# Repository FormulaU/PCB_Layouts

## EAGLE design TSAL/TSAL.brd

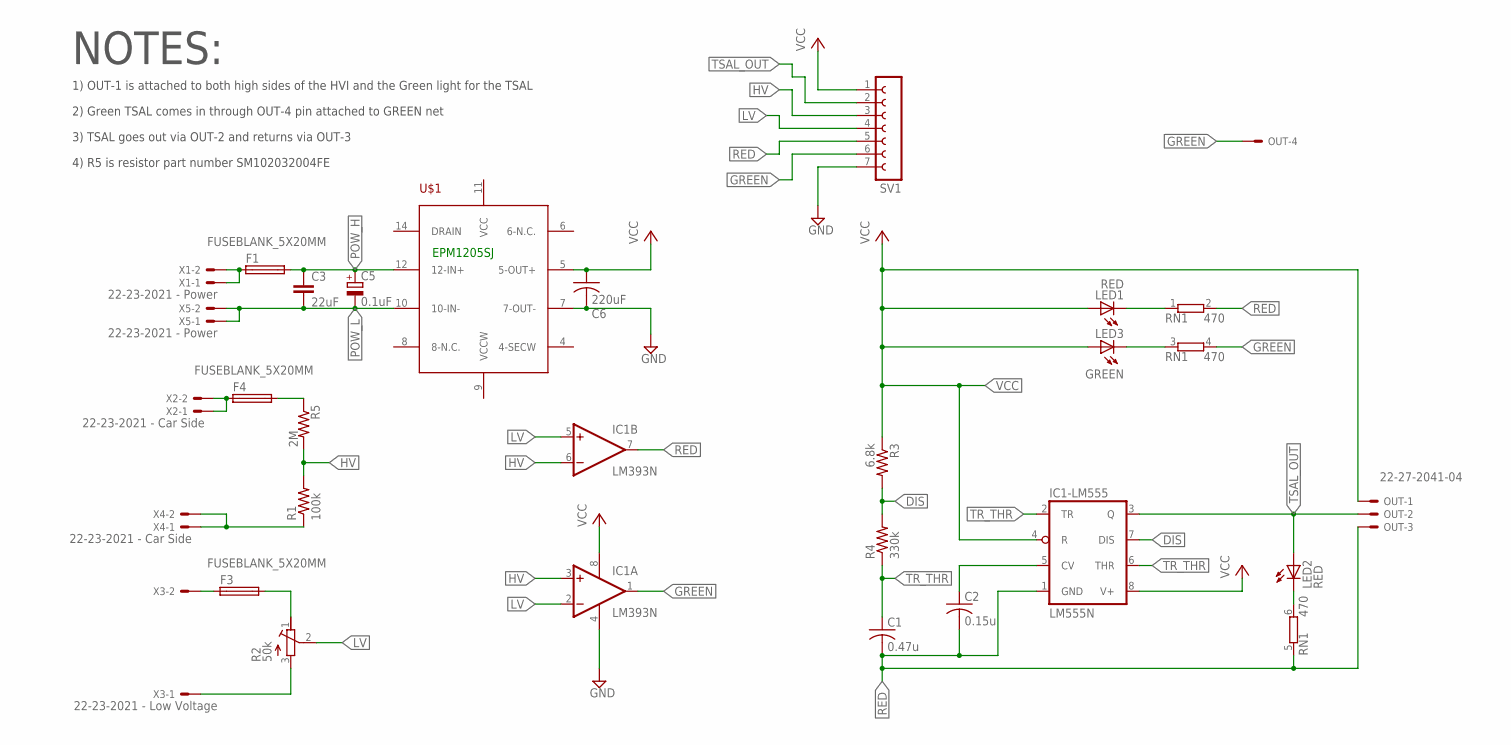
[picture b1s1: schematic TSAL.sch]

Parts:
C1: 0.47u; C050-075X075
C2: 0.15u; C050-075X075
C3: 22uF; C150-091X182
C5: 0.1uF; E7,5-16
C6: 220uF; C050-055X075
F1, F3, F4: FUSEBLANK_5X20MM; FUSE_HOLDER_5X20MM
IC1: LM393N; DIL08
IC1-LM555: LM555N; DIL08
LED1, LED2: RED; LED3MM
LED3: GREEN; LED3MM
OUT: 22-27-2041-04; 6410-04
R1: 100k; 0207/10
R2: 50k; RTRIM3006P
R3: 6.8k; 0309/12
R4: 330k; 0309/12
R5: 2M; 0207/10
RN1: 470; SIL6
SV1: FE07W
U$1: EPM1205SJ
X1, X5: 22-23-2021 - Power; 22-23-2021
X2, X4: 22-23-2021 - Car Side; 22-23-2021
X3: 22-23-2021 - Low Voltage; 22-23-2021

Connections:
DIS: IC1-LM555.7 (DIS), R3.2, R4.2
GND: C6.2, IC1.4 (V-), SV1.7, U$1.7 (7-OUT-)
GREEN: IC1.1 (OUT), OUT.4, RN1.4 (2), SV1.6
HV: IC1.3 (+IN), IC1.6 (-IN), R1.2, R5.2, SV1.3
LV: IC1.2 (-IN), IC1.5 (+IN), R2.2 (S), SV1.4
unnamed: R1.1, X4.1, X4.2
unnamed: F3.2, R2.1 (E)
unnamed: R2.3 (A), X3.1
unnamed: F4.1, X2.1, X2.2
unnamed: F3.1, X3.2
unnamed: LED3.K (C), RN1.3 (1)
unnamed: F1.1, X1.1, X1.2
unnamed: F4.2, R5.1
unnamed: C2.1, IC1-LM555.5 (CV)
unnamed: LED2.K (C), RN1.6 (2)
unnamed: LED1.K (C), RN1.1
POW_H: C3.1, C5.+, F1.2, U$1.12 (12-IN+)
POW_L: C3.2, C5.-, U$1.10 (10-IN-), X5.1, X5.2
RED: C1.2, C2.2, IC1.7 (OUT), IC1-LM555.1 (GND), OUT.3, RN1.2, RN1.5 (1), SV1.5
TR_THR: C1.1, IC1-LM555.2 (TR), IC1-LM555.6 (THR), R4.1
TSAL_OUT: IC1-LM555.3 (Q), LED2.A, OUT.2, SV1.2
VCC: C6.1, IC1.8 (V+), IC1-LM555.4 (R), IC1-LM555.8 (V+), LED1.A, LED3.A, OUT.1, R3.1, SV1.1, U$1.5 (5-OUT+)

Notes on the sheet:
EPM1205SJ
NOTES:
1) OUT-1 is attached to both high sides of the HVI and the Green light for the TSAL
2) Green TSAL comes in through OUT-4 pin attached to GREEN net
3) TSAL goes out via OUT-2 and returns via OUT-3
4) R5 is resistor part number SM102032004FE

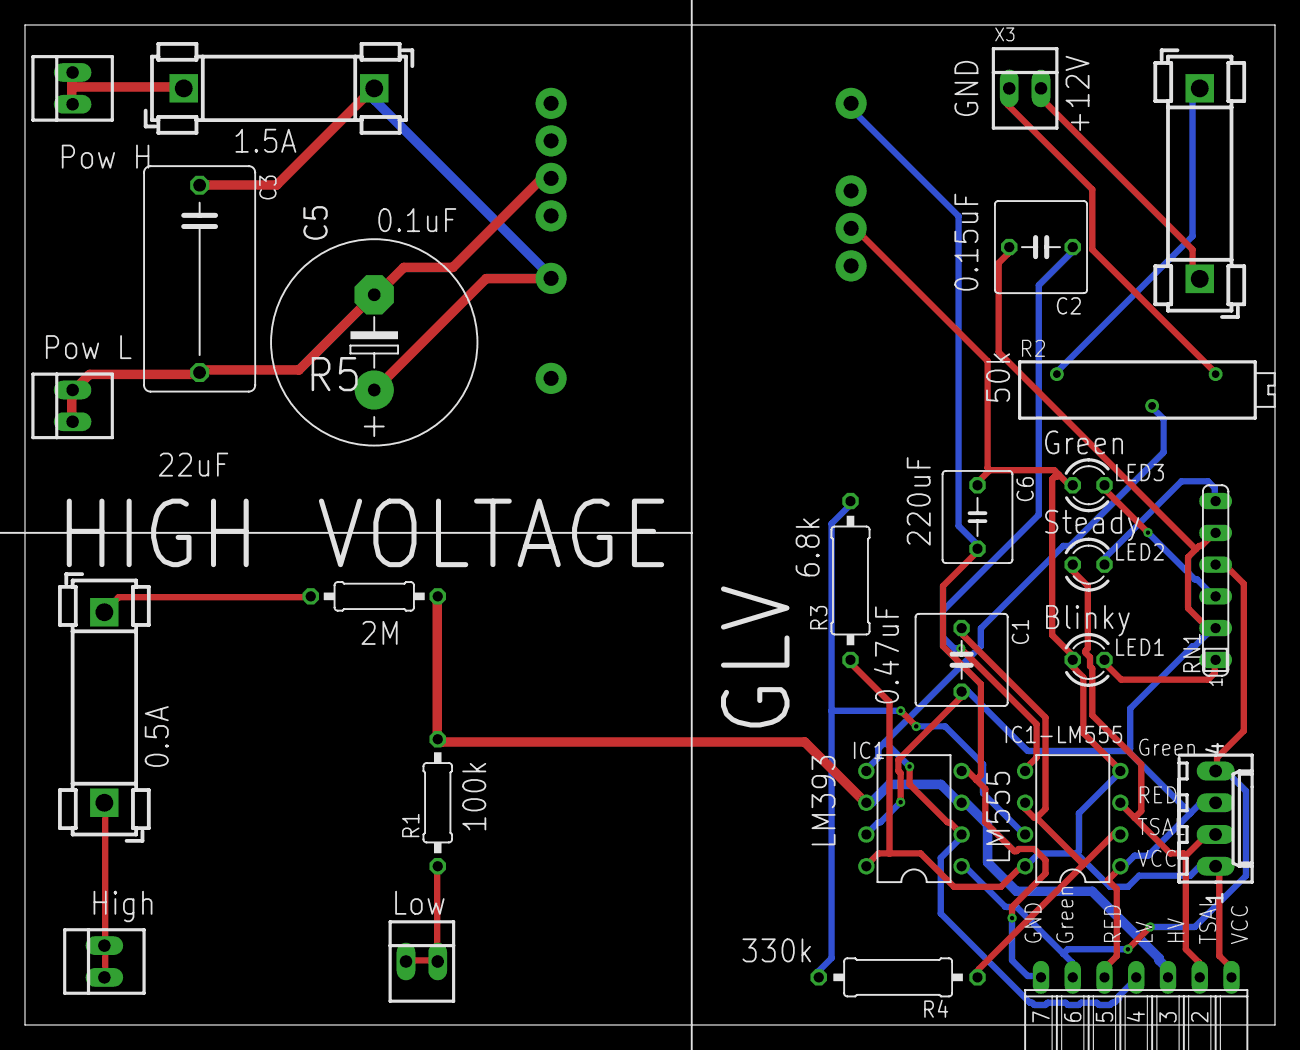
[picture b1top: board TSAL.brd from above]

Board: 2 copper layers, 100.0 x 80.0 mm, 27 parts (0 on the bottom side), 22 nets.

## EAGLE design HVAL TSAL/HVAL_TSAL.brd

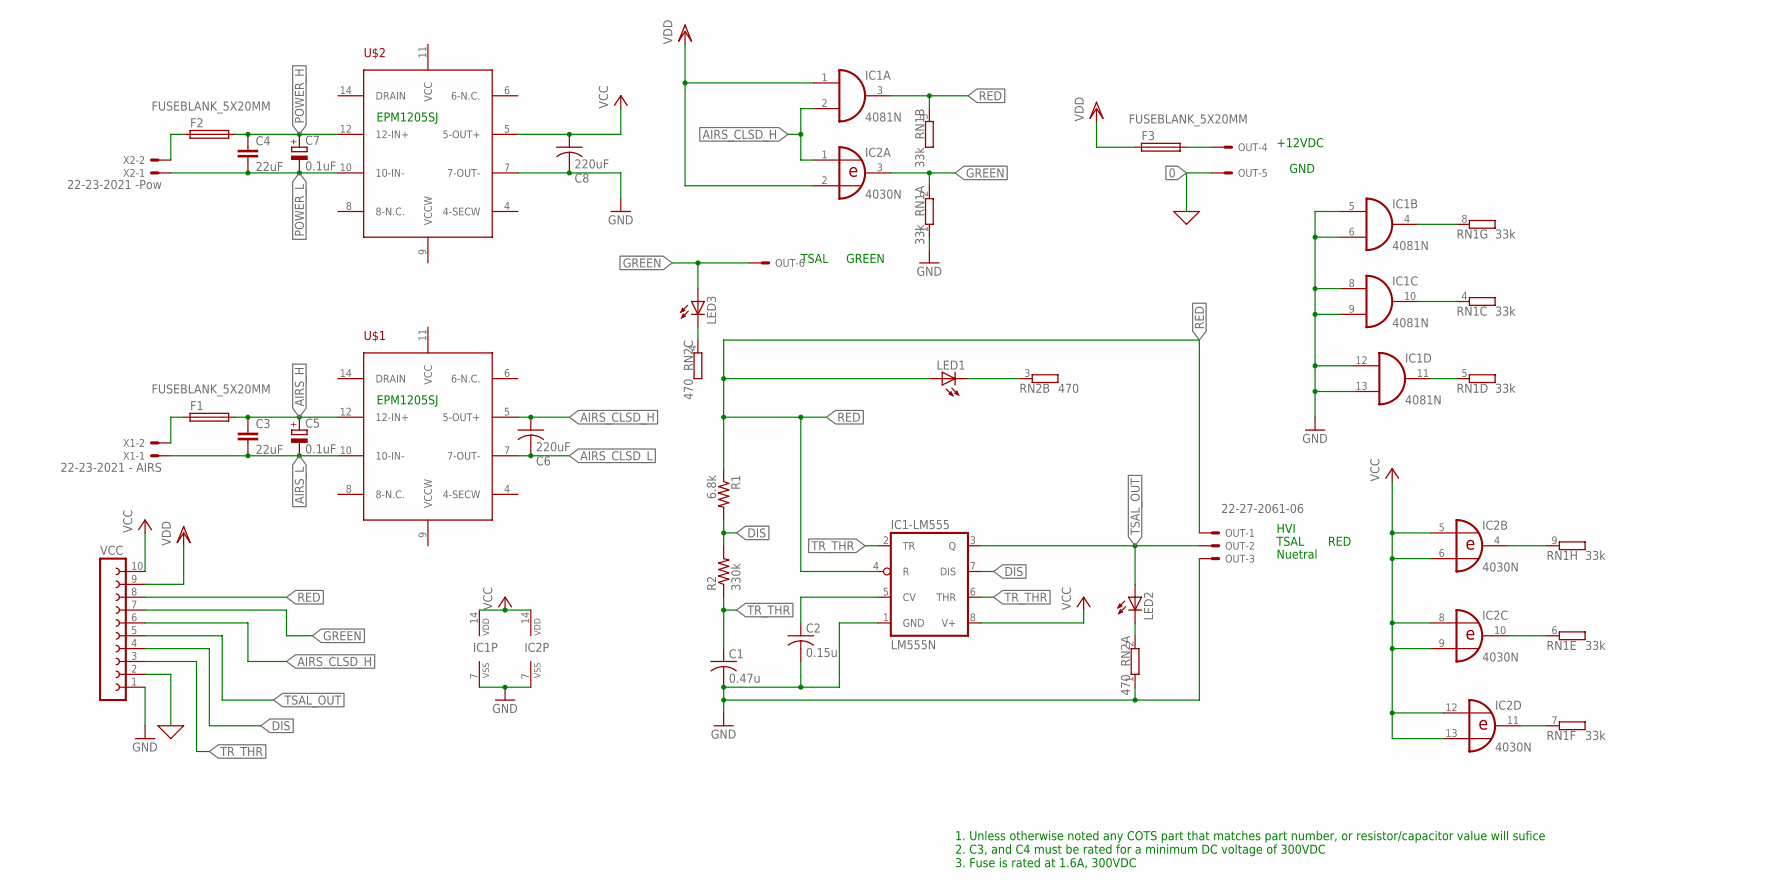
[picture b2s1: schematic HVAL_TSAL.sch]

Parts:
C1: 0.47u; C050-075X075
C2: 0.15u; C050-075X075
C3, C4: 22uF; C150-091X182
C5, C7: 0.1uF; E7,5-16
C6, C8: 220uF; C050-055X075
F1, F2, F3: FUSEBLANK_5X20MM; FUSE_HOLDER_5X20MM
IC1: 4081N; DIL14
IC1-LM555: LM555N; DIL08
IC2: 4030N; DIL14
LED1, LED2, LED3: LED3MM
OUT: 22-27-2061-06; 6410-06
R1: 6.8k; 0309/12
R2: 330k; 0309/12
RN1: 33k; SIL9
RN2: 470; SIL4
U$1, U$2: EPM1205SJ
VCC: FE10-1; FE10
X1: 22-23-2021 - AIRS; 22-23-2021
X2: 22-23-2021 -Pow; 22-23-2021

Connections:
0: OUT.5, VCC.2
AIRS_CLSD_H: C6.1, IC1.2 (I1), IC2.1 (I0), U$1.5 (5-OUT+), VCC.6
AIRS_CLSD_L: C6.2, U$1.7 (7-OUT-)
AIRS_H: C3.1, C5.+, F1.2, U$1.12 (12-IN+)
AIRS_L: C3.2, C5.-, U$1.10 (10-IN-), X1.1
DIS: IC1-LM555.7 (DIS), R1.2, R2.2, VCC.4
GND: C1.2, C2.2, C8.2, IC1.5 (I0), IC1.6 (I1), IC1.7 (VSS), IC1.8 (I0), IC1.9 (I1), IC1.12 (I0), IC1.13 (I1), IC1-LM555.1 (GND), IC2.7 (VSS), OUT.3, RN1.1, RN2.1, U$2.7 (7-OUT-), VCC.1
GREEN: IC2.3 (O), LED3.A, OUT.6, RN1.2, VCC.7
unnamed: LED2.K (C), RN2.2
unnamed: IC2.10 (O), RN1.6 (2)
unnamed: IC1.11 (O), RN1.5 (2)
unnamed: F2.1, X2.2
unnamed: F3.2, OUT.4
unnamed: IC1.10 (O), RN1.4 (2)
unnamed: C2.1, IC1-LM555.5 (CV)
unnamed: IC2.4 (O), RN1.9 (2)
unnamed: IC1.4 (O), RN1.8 (2)
unnamed: F1.1, X1.2
unnamed: IC2.11 (O), RN1.7 (2)
unnamed: LED1.K (C), RN2.3 (2)
unnamed: LED3.K (C), RN2.4 (2)
POWER_H: C4.1, C7.+, F2.2, U$2.12 (12-IN+)
POWER_L: C4.2, C7.-, U$2.10 (10-IN-), X2.1
RED: IC1.3 (O), IC1-LM555.4 (R), LED1.A, OUT.1, R1.1, RN1.3 (2), VCC.8
TR_THR: C1.1, IC1-LM555.2 (TR), IC1-LM555.6 (THR), R2.1, VCC.3
TSAL_OUT: IC1-LM555.3 (Q), LED2.A, OUT.2, VCC.5
VCC: C8.1, IC1.14 (VDD), IC1-LM555.8 (V+), IC2.5 (I0), IC2.6 (I1), IC2.8 (I0), IC2.9 (I1), IC2.12 (I0), IC2.13 (I1), IC2.14 (VDD), U$2.5 (5-OUT+), VCC.10
VDD: F3.1, IC1.1 (I0), IC2.2 (I1), VCC.9

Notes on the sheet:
EPM1205SJ
1. Unless otherwise noted any COTS part that matches part number, or resistor/capacitor value will sufice 2. C3, and C4 must be rated for a minimum DC voltage of 300VDC 3. Fuse is rated at 1.6A, 300VDC
TSAL
HVI
Nuetral
+12VDC
GND
RED
TSAL GREEN

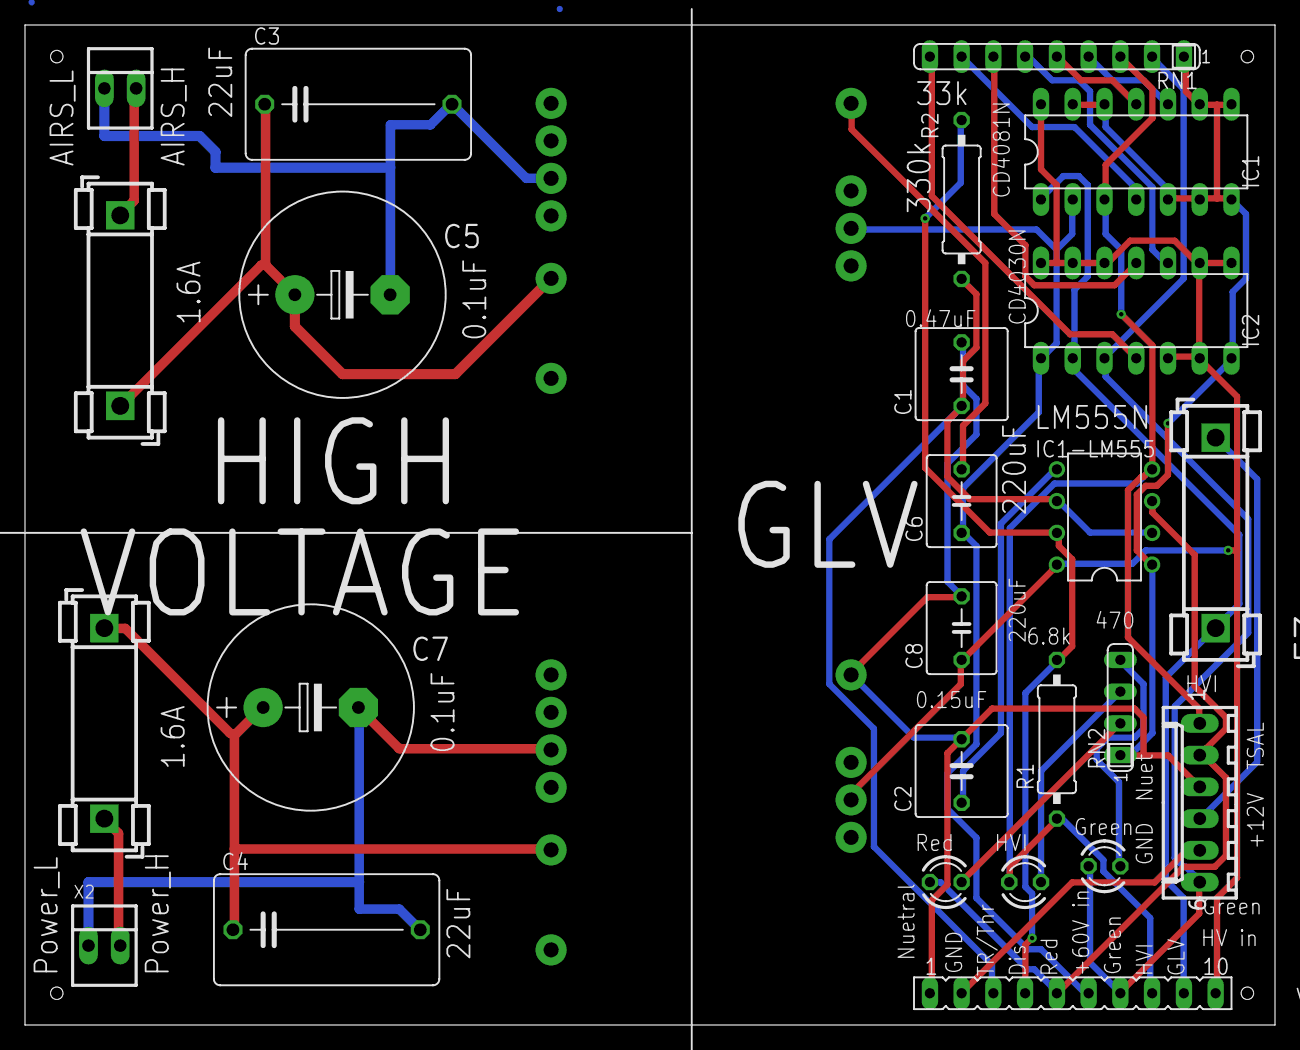
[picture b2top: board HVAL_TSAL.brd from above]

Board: 2 copper layers, 100.0 x 80.0 mm, 27 parts (0 on the bottom side), 28 nets.

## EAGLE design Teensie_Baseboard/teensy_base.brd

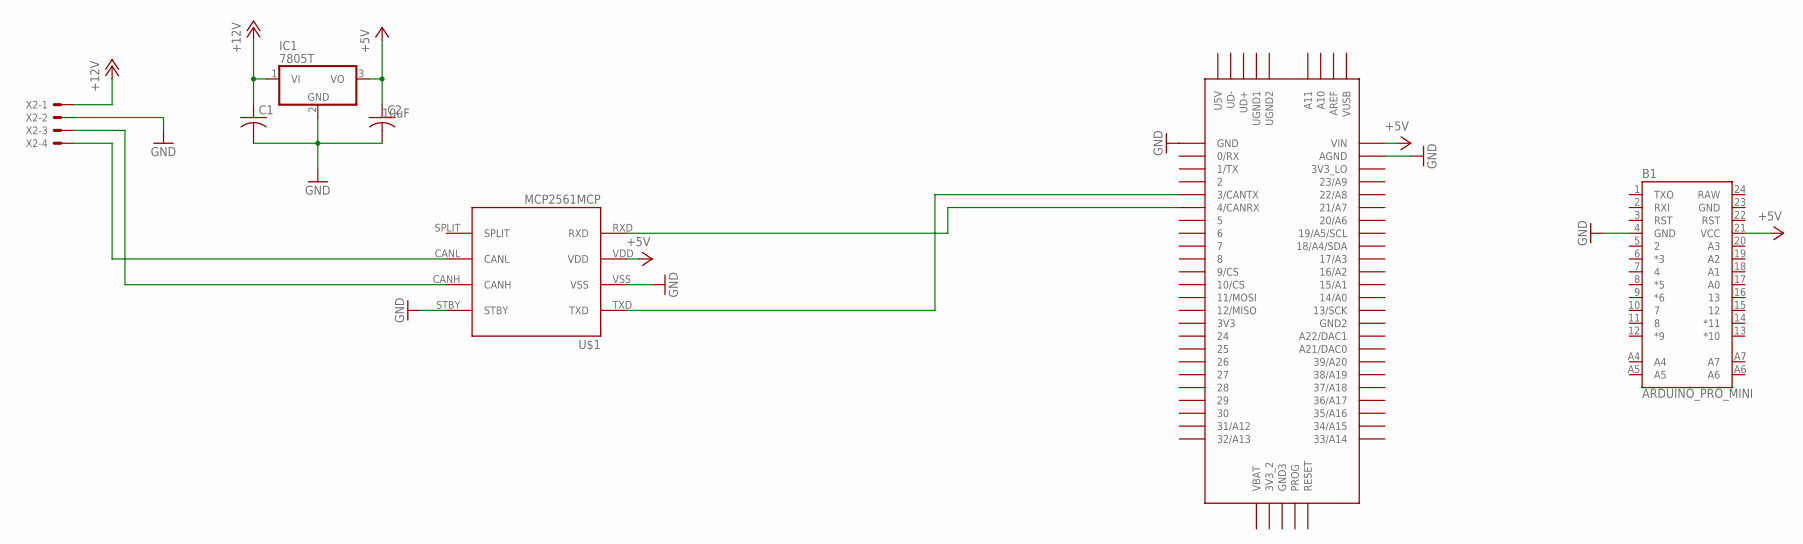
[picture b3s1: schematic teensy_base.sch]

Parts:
B1: ARDUINO_PRO_MINI
C1, C2: C-USC1206; C1206
IC1: 7805T; TO220H
U$1: MCP2561MCP; MCP2561_PDIP
U$2: TEENSY_3.5/3.6
X2: KK-156-4

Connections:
+5V: B1.21 (VCC), C2.1, IC1.3 (VO), U$1.VDD, U$2.VIN
+12V: C1.1, IC1.1 (VI), X2.1
GND: B1.4 (GND), B1.23 (GND), C1.2, C2.2, IC1.2 (GND), U$1.STBY, U$1.VSS, U$2.AGND, U$2.GND, X2.2
unnamed: U$1.RXD, U$2.4/CANRX
unnamed: U$1.TXD, U$2.3/CANTX
unnamed: U$1.CANH, X2.3
unnamed: U$1.CANL, X2.4
RAW: B1.24 (RAW)

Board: 2 copper layers, 7 parts (0 on the bottom side), 7 nets, no tracks yet.

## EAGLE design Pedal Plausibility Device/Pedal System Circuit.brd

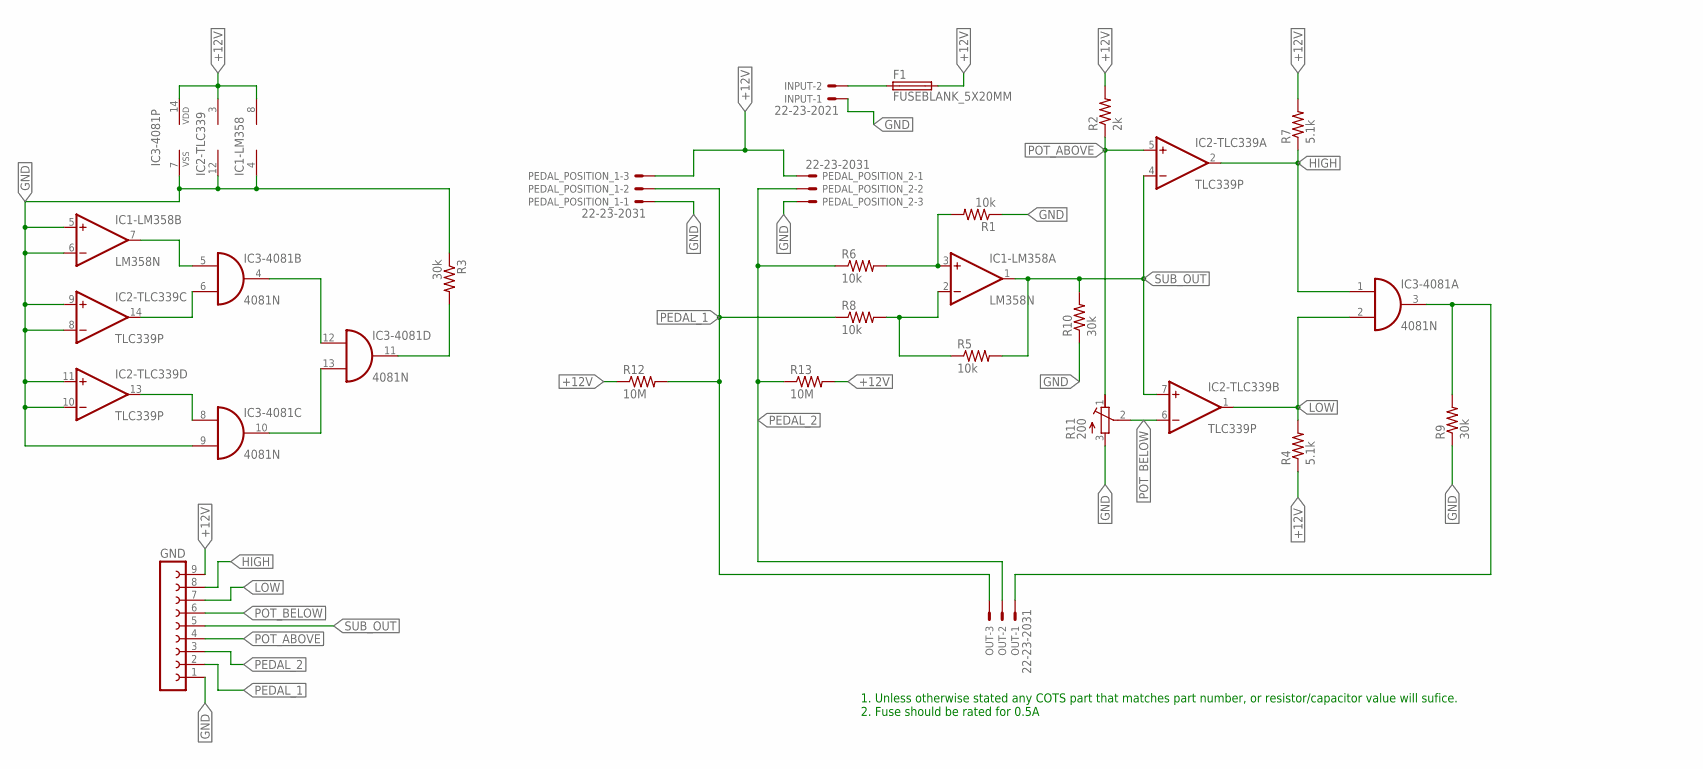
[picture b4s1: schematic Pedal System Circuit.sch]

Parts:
F1: FUSEBLANK_5X20MM; FUSE_HOLDER_5X20MM
GND: FE09W
IC1-LM358: LM358N; DIL08
IC2-TLC339: TLC339P; DIL14
IC3-4081: 4081N; DIL14
INPUT: 22-23-2021
OUT: 22-23-2031
PEDAL_POSITION_1, PEDAL_POSITION_2: 22-23-2031
R1, R5, R6, R8: 10k; 0207/12
R2: 2k; 0309/12
R3, R9, R10: 30k; 0207/12
R4, R7: 5.1k; 0207/12
R11: 200; RTRIM43P
R12, R13: 10M; 0207/12

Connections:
+12V: F1.2, GND.9, IC1-LM358.8 (V+), IC2-TLC339.3 (V+), IC3-4081.14 (VDD), PEDAL_POSITION_1.3, PEDAL_POSITION_2.1, R2.2, R4.1, R7.2, R12.1, R13.2
GND: GND.1, IC1-LM358.4 (V-), IC1-LM358.5 (+IN), IC1-LM358.6 (-IN), IC2-TLC339.8 (-IN), IC2-TLC339.9 (+IN), IC2-TLC339.10 (-IN), IC2-TLC339.11 (+IN), IC2-TLC339.12 (V-), IC3-4081.7 (VSS), IC3-4081.9 (I1), INPUT.1, PEDAL_POSITION_1.1, PEDAL_POSITION_2.3, R1.1, R3.1, R9.1, R10.1, R11.3 (A)
HIGH: GND.8, IC2-TLC339.2 (OUT), IC3-4081.1 (I0), R7.1
LOW: GND.7, IC2-TLC339.1 (OUT), IC3-4081.2 (I1), R4.2
unnamed: IC3-4081.10 (O), IC3-4081.13 (I1)
unnamed: IC3-4081.4 (O), IC3-4081.12 (I0)
unnamed: IC1-LM358.3 (+IN), R1.2, R6.2
unnamed: IC3-4081.3 (O), OUT.1, R9.2
unnamed: IC3-4081.11 (O), R3.2
unnamed: IC1-LM358.7 (OUT), IC3-4081.5 (I0)
unnamed: F1.1, INPUT.2
unnamed: IC2-TLC339.13 (OUT), IC3-4081.8 (I0)
unnamed: IC2-TLC339.14 (OUT), IC3-4081.6 (I1)
unnamed: IC1-LM358.2 (-IN), R5.1, R8.2
PEDAL_1: GND.2, OUT.3, PEDAL_POSITION_1.2, R8.1, R12.2
PEDAL_2: GND.3, OUT.2, PEDAL_POSITION_2.2, R6.1, R13.1
POT_ABOVE: GND.4, IC2-TLC339.5 (+IN), R2.1, R11.1 (E)
POT_BELOW: GND.6, IC2-TLC339.6 (-IN), R11.2 (S)
SUB_OUT: GND.5, IC1-LM358.1 (OUT), IC2-TLC339.4 (-IN), IC2-TLC339.7 (+IN), R5.2, R10.2

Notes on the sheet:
IC2-TLC339
IC1-LM358
1. Unless otherwise stated any COTS part that matches part number, or resistor/capacitor value will sufice. 2. Fuse should be rated for 0.5A

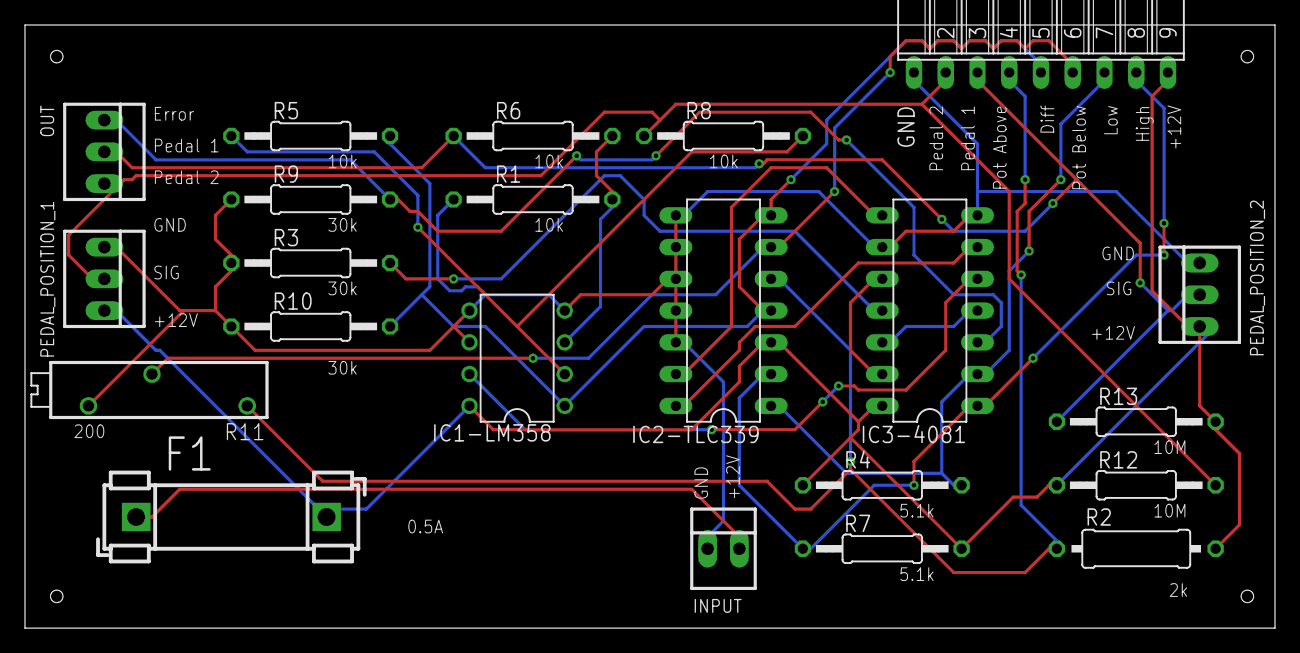
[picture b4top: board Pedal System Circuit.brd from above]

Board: 2 copper layers, 100.0 x 48.2 mm, 22 parts (0 on the bottom side), 19 nets.

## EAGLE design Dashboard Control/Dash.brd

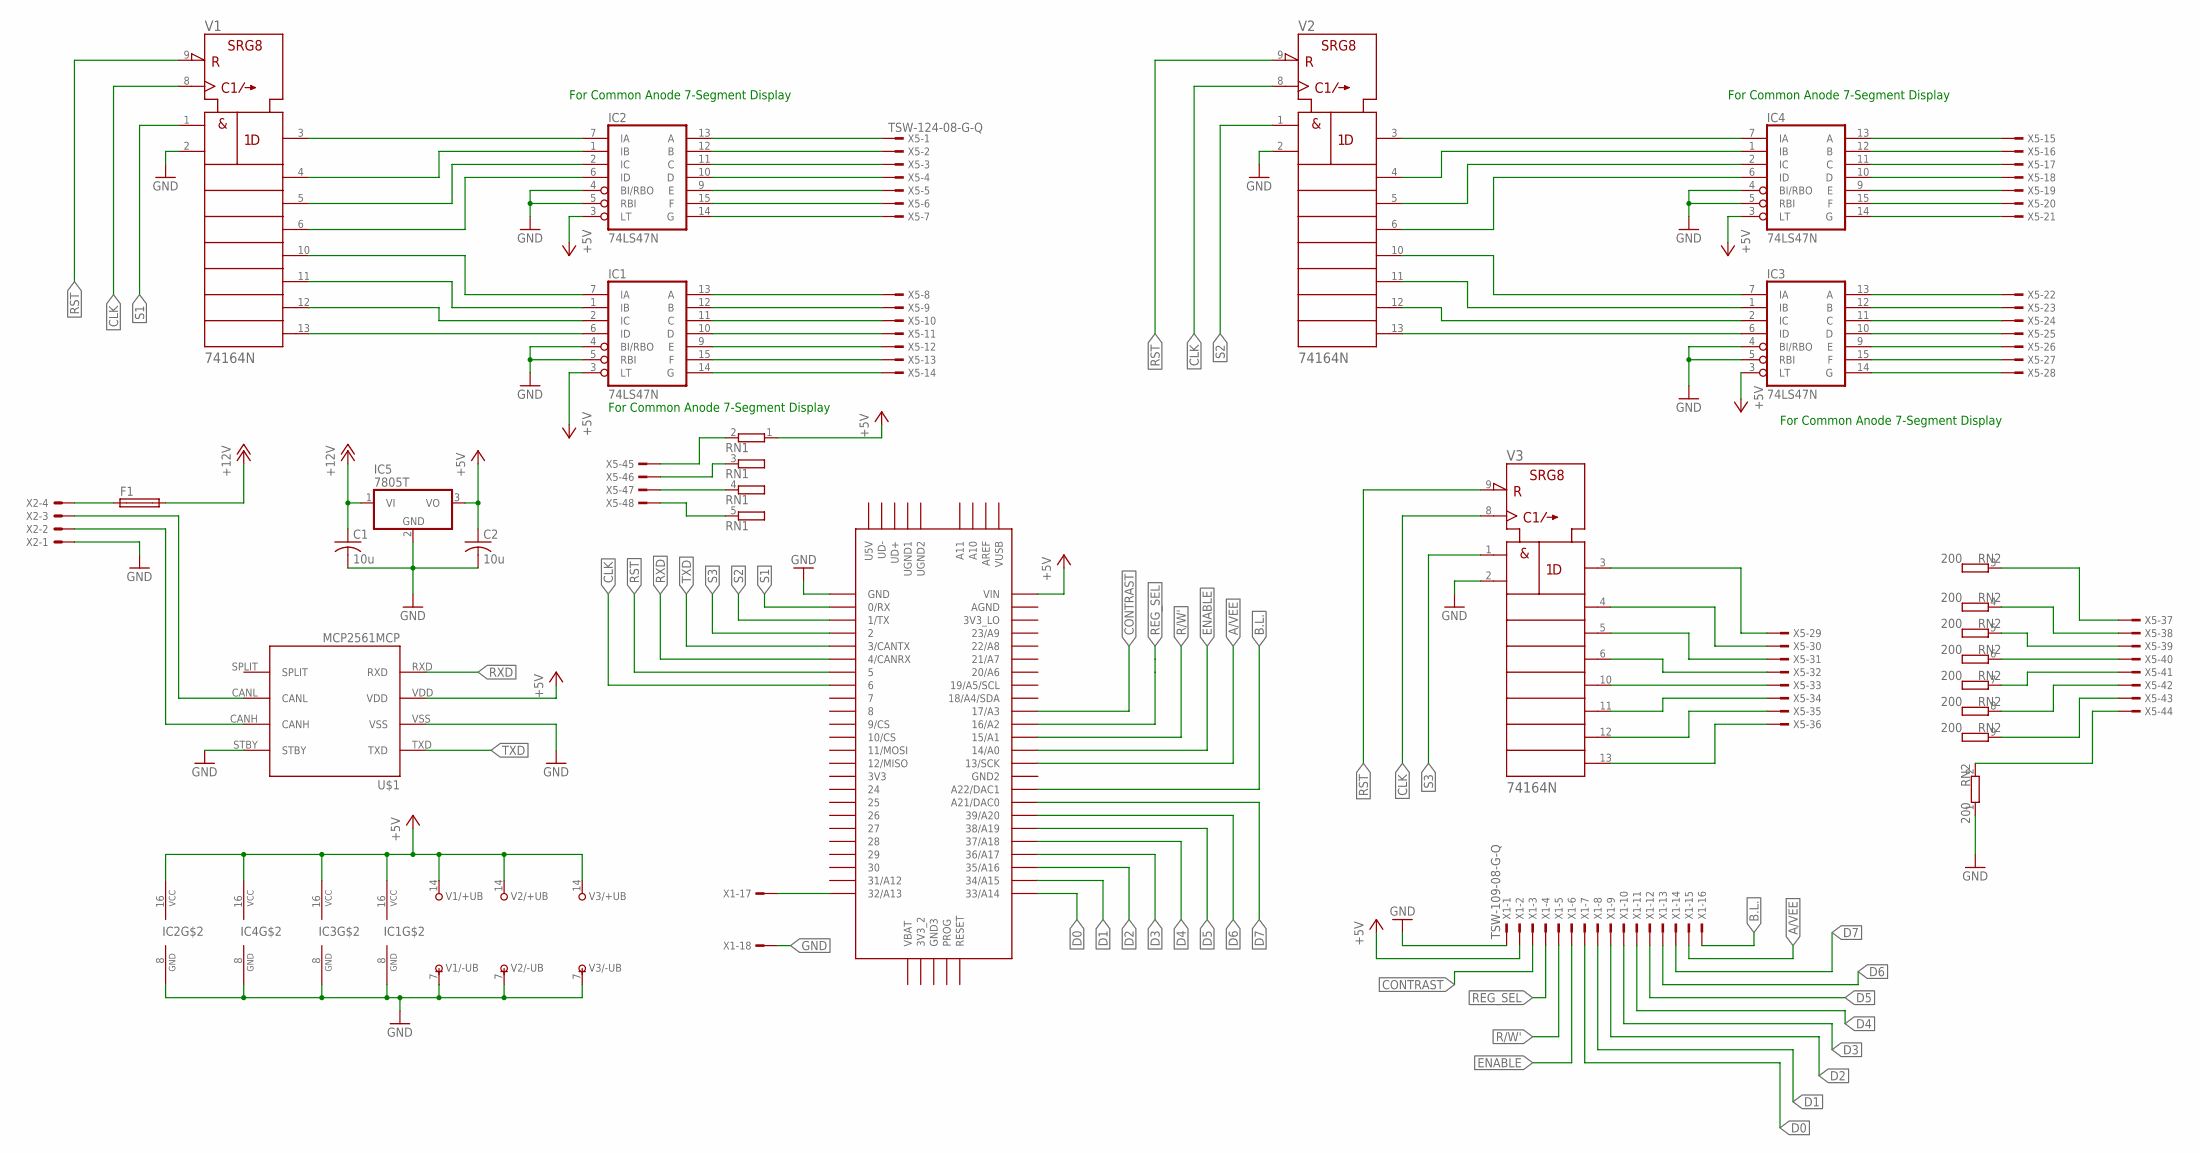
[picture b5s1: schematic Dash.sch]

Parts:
C1, C2: 10u; C050-024X044
F1: FUSEBLANK_5X20MM; FUSE_HOLDER_5X20MM
IC1, IC2, IC3, IC4: 74LS47N; DIL16
IC5: 7805T; TO220H
RN1: GE04RP; SIL5
RN2: 200; SIL9
U$1: MCP2561MCP; MCP2561_PDIP
U$2: TEENSY_3.5/3.6
V1, V2, V3: 74164N; DIL14
X1: TSW-109-08-G-Q; TSW-109-XX-G-Q
X2: KK-156-4
X5: TSW-124-08-G-Q; TSW-124-XX-G-Q

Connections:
+5V: C2.1, IC1.3 (LT), IC1.16 (VCC), IC2.3 (LT), IC2.16 (VCC), IC3.3 (LT), IC3.16 (VCC), IC4.3 (LT), IC4.16 (VCC), IC5.3 (VO), RN1.1, U$1.VDD, U$2.VIN, V1.14 (+UB), V2.14 (+UB), V3.14 (+UB), X1.2
+12V: C1.1, F1.2, IC5.1 (VI)
A1: IC2.13 (A), X5.1
A2: IC1.13 (A), X5.8
A3: IC3.13 (A), X5.22
A4: IC4.13 (A), X5.15
A/VEE: U$2.13/SCK, X1.15
B1: IC2.12 (B), X5.2
B2: IC1.12 (B), X5.9
B3: IC3.12 (B), X5.23
B4: IC4.12 (B), X5.16
B.L.: U$2.A22/DAC1, X1.16
C1: IC2.11 (C), X5.3
C2: IC1.11 (C), X5.10
C3: IC3.11 (C), X5.24
C4: IC4.11 (C), X5.17
CAN_H: U$1.CANH, X2.2
CAN_L: U$1.CANL, X2.3
CLK: U$2.6, V1.8 (CLK), V2.8 (CLK), V3.8 (CLK)
CONTRAST: U$2.17/A3, X1.3
D0: U$2.33/A14, X1.7
D1: IC2.10 (D), U$2.34/A15, X1.8, X5.4
D2: IC1.10 (D), U$2.35/A16, X1.9, X5.11
D3: IC3.10 (D), U$2.36/A17, X1.10, X5.25
D4: IC4.10 (D), U$2.37/A18, X1.11, X5.18
D5: U$2.38/A19, X1.12
D6: U$2.39/A20, X1.13
D7: U$2.21/DAC0 (A21/DAC0), X1.14
E1: IC2.9 (E), X5.5
E2: IC1.9 (E), X5.12
E3: IC3.9 (E), X5.26
E4: IC4.9 (E), X5.19
ENABLE: U$2.14/A0, X1.6
F1: IC2.15 (F), X5.6
F2: IC1.15 (F), X5.13
F3: IC3.15 (F), X5.27
F4: IC4.15 (F), X5.20
G1: IC2.14 (G), X5.7
G2: IC1.14 (G), X5.14
G3: IC3.14 (G), X5.28
G4: IC4.14 (G), X5.21
GND: C1.2, C2.2, IC1.4 (BI/RBO), IC1.5 (RBI), IC1.8 (GND), IC2.4 (BI/RBO), IC2.5 (RBI), IC2.8 (GND), IC3.4 (BI/RBO), IC3.5 (RBI), IC3.8 (GND), IC4.4 (BI/RBO), IC4.5 (RBI), IC4.8 (GND), IC5.2 (GND), RN2.1, U$1.STBY, U$1.VSS, U$2.GND, V1.2 (B), V1.7 (-UB), V2.2 (B), V2.7 (-UB), V3.2 (B), V3.7 (-UB), X1.1, X1.18, X2.1
unnamed: RN2.6 (2), X5.40
unnamed: V3.4 (QB), X5.30
unnamed: V3.5 (QC), X5.31
unnamed: V3.6 (QD), X5.32
unnamed: V3.10 (QE), X5.33
unnamed: V3.11 (QF), X5.34
unnamed: V3.12 (QG), X5.35
unnamed: V3.13 (QH), X5.36
unnamed: RN2.5 (2), X5.39
unnamed: RN2.4 (2), X5.38
unnamed: RN2.3 (2), X5.37
unnamed: RN2.7 (2), X5.41
unnamed: RN2.8 (2), X5.42
unnamed: RN2.9 (2), X5.43
unnamed: RN2.2, X5.44
unnamed: U$2.32/A13, X1.17
unnamed: F1.1, X2.4
unnamed: RN1.2, X5.45
unnamed: RN1.3 (2), X5.46
unnamed: RN1.4 (2), X5.47
unnamed: RN1.5 (2), X5.48
unnamed: IC4.7 (IA), V2.3 (QA)
unnamed: IC4.1 (IB), V2.4 (QB)
unnamed: IC4.2 (IC), V2.5 (QC)
unnamed: IC4.6 (ID), V2.6 (QD)
unnamed: IC3.7 (IA), V2.10 (QE)
unnamed: IC3.2 (IC), V2.12 (QG)
unnamed: IC3.6 (ID), V2.13 (QH)
unnamed: IC2.7 (IA), V1.3 (QA)
unnamed: IC2.1 (IB), V1.4 (QB)
unnamed: IC2.2 (IC), V1.5 (QC)
unnamed: IC2.6 (ID), V1.6 (QD)
unnamed: IC1.7 (IA), V1.10 (QE)
unnamed: IC1.1 (IB), V1.11 (QF)
unnamed: IC1.2 (IC), V1.12 (QG)
unnamed: IC1.6 (ID), V1.13 (QH)
unnamed: IC3.1 (IB), V2.11 (QF)
unnamed: V3.3 (QA), X5.29
R/W': U$2.15/A1, X1.5
REG_SEL: U$2.16/A2, X1.4
RST: U$2.5, V1.9 (!CLR), V2.9 (!CLR), V3.9 (!CLR)
RXD: U$1.RXD, U$2.4/CANRX
S1: U$2.0/RX, V1.1 (A)
S2: U$2.1/TX, V2.1 (A)
S3: U$2.2, V3.1 (A)
TXD: U$1.TXD, U$2.3/CANTX

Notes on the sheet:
For Common Anode 7-Segment Display

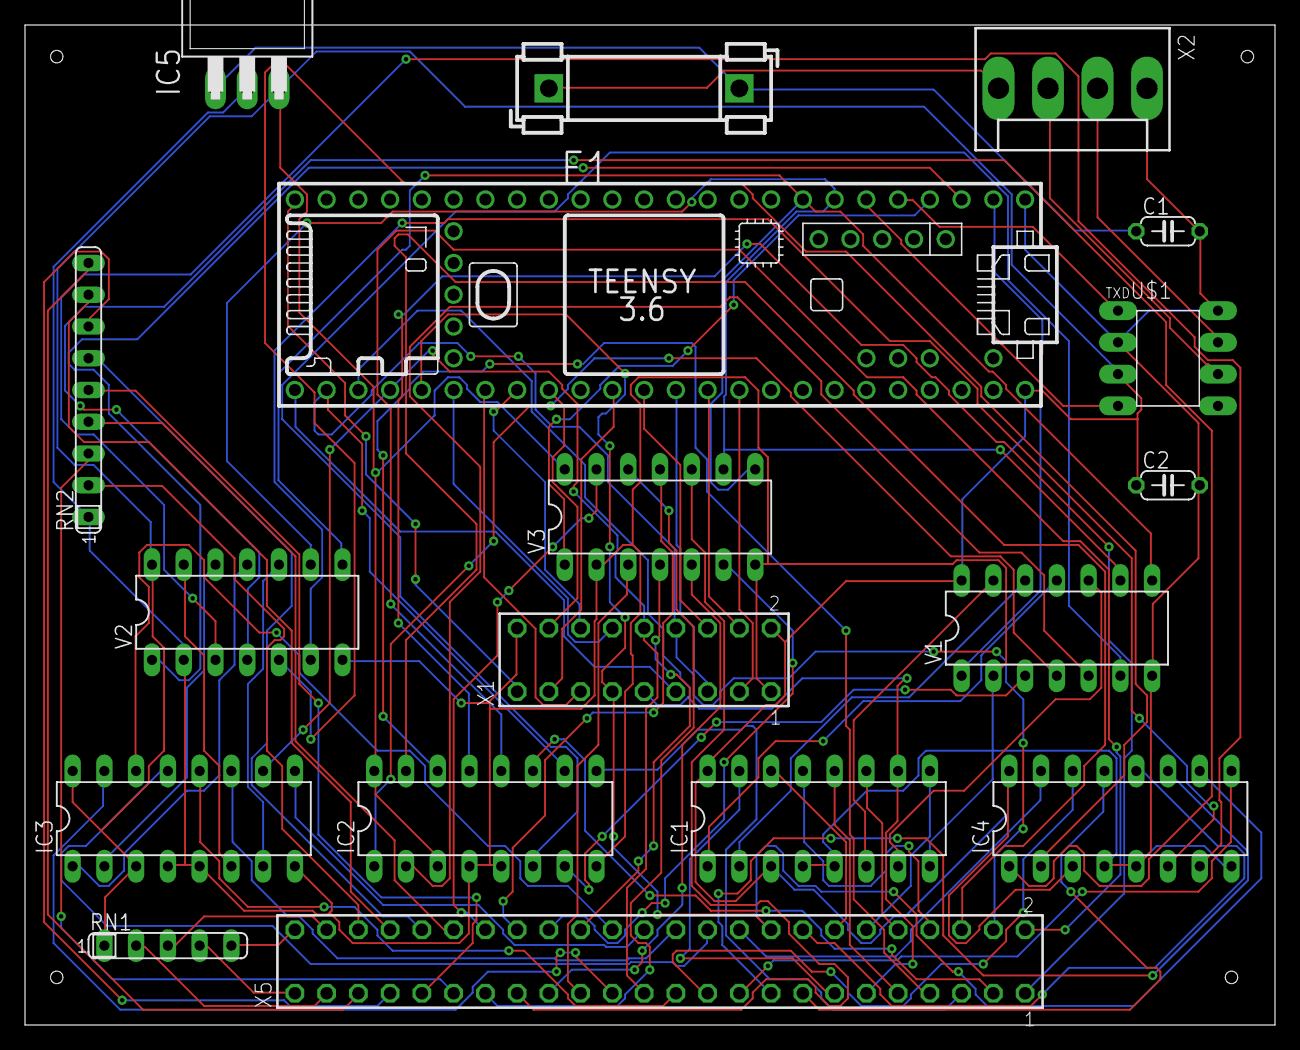
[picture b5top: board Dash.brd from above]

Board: 2 copper layers, 100.0 x 80.0 mm, 18 parts (0 on the bottom side), 88 nets.

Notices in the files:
parts and their libraries:
SparkFun-Boards: Licensing: Creative Commons ShareAlike 4.0 International - https://creativecommons.org/licenses/by-sa/4.0
